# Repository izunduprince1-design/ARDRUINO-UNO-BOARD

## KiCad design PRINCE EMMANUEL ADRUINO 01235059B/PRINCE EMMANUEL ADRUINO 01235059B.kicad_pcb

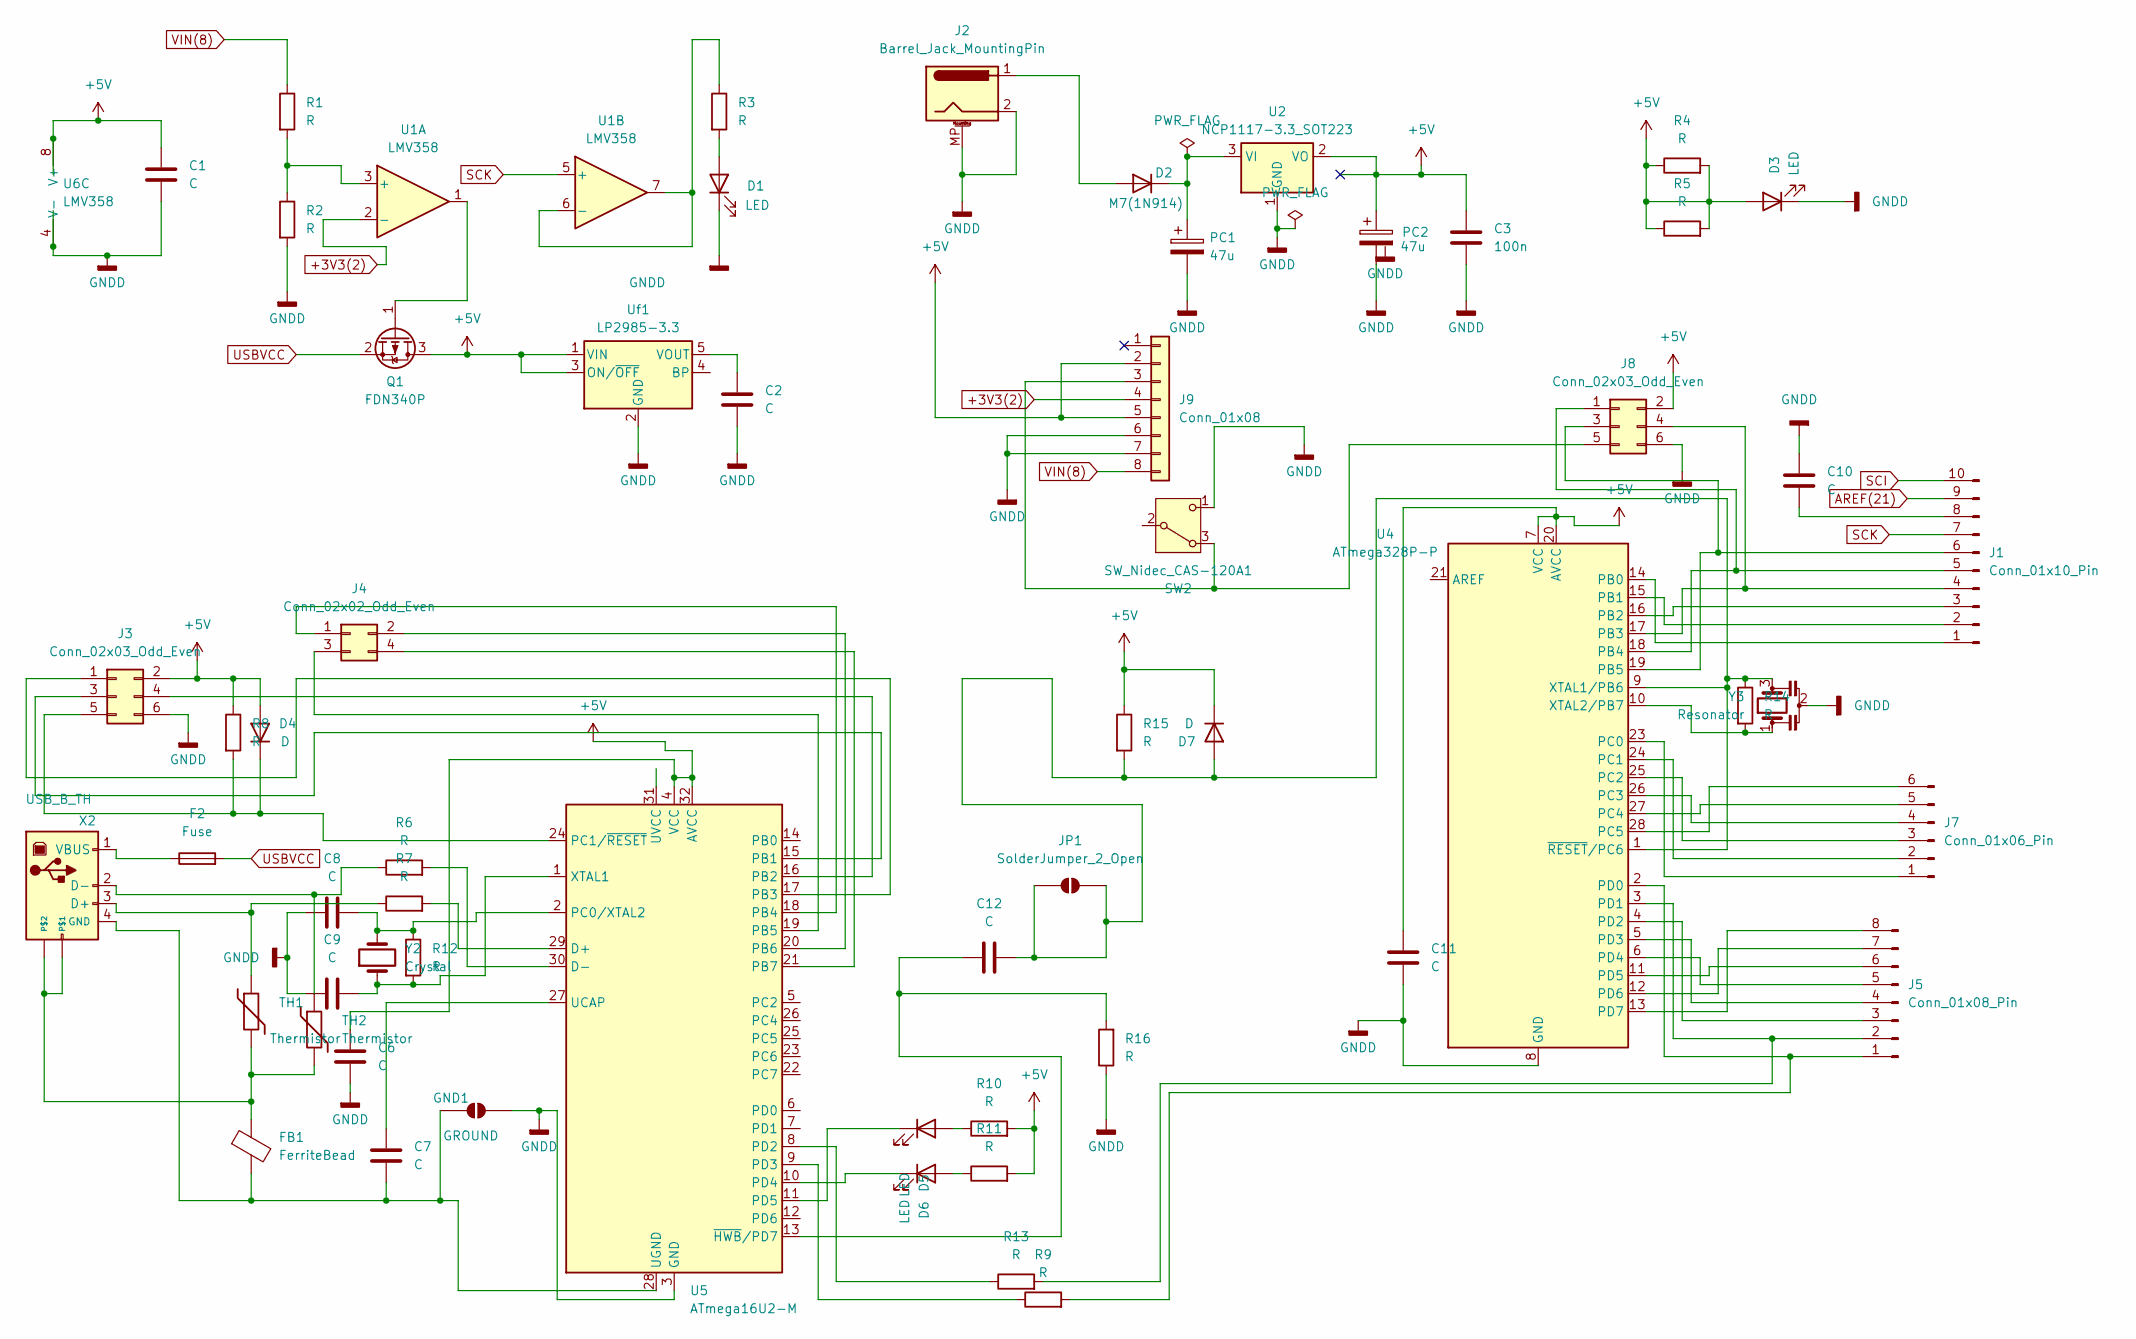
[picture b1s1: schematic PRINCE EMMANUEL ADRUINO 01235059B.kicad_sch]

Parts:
C1, C6, C7, C8, C9, C10, C11, C12: C; C_0603_1608Metric_Pad1.08x0.95mm_HandSolder
C2: C; C_01005_0402Metric
C3: 100n; C_0805_2012Metric_Pad1.18x1.45mm_HandSolder
D1, D3, D5, D6: LED; LED_0805_2012Metric_Pad1.15x1.40mm_HandSolder
D2: M7(1N914); D_SC-80
D4: D; D_01005_0402Metric
D7: D; D_SOD-123
F2: Fuse; Fuse_2920_7451Metric
FB1: FerriteBead; L_0805_2012Metric_Pad1.05x1.20mm_HandSolder
GND1: GROUND; SolderJumper-2_P1.3mm_Open_RoundedPad1.0x1.5mm
J1: Conn_01x10_Pin; PinSocket_1x10_P2.54mm_Vertical
J2: Barrel_Jack_MountingPin; BarrelJack_Horizontal
J3: Conn_02x03_Odd_Even; PinHeader_2x03_P2.54mm_Vertical_SMD
J4: Conn_02x02_Odd_Even; PinSocket_2x02_P2.54mm_Vertical
J5: Conn_01x08_Pin; PinHeader_1x08_P2.54mm_Vertical
J7: Conn_01x06_Pin; PinSocket_1x06_P2.54mm_Vertical
J8: Conn_02x03_Odd_Even; PinHeader_2x03_P2.54mm_Vertical
J9: Conn_01x08; PinSocket_1x08_P2.54mm_Vertical
JP1: SolderJumper_2_Open; SolderJumper-2_P1.3mm_Open_RoundedPad1.0x1.5mm
PC1, PC2: 47u; CP_Elec_6.3x5.4
Q1: FDN340P; SOT-23
R1, R2, R3, R4, R5, R6, R7, R9, R10, R11, R12, R13, R14, R15, R16: R; R_0201_0603Metric_Pad0.64x0.40mm_HandSolder
R8: R; R_0805_2012Metric_Pad1.20x1.40mm_HandSolder
SW2: SW_Nidec_CAS-120A1; SW_Push_1P1T_NO_CK_PTS125Sx43SMTR
TH1, TH2: Thermistor; R_0201_0603Metric_Pad0.64x0.40mm_HandSolder
U1, U6: LMV358; MSOP-8_3x3mm_P0.65mm
U2: NCP1117-3.3_SOT223; SOT-223-3_TabPin2
U4: ATmega328P-P; DIP-28_W7.62mm
U5: ATmega16U2-M; QFN-32-1EP_5x5mm_P0.5mm_EP3.1x3.1mm
Uf1: LP2985-3.3; SOT-23-5
X2: USB_B_TH; USB_B_TE_5787834_Vertical
Y2: Crystal; Crystal_HC49-4H_Vertical
Y3: Resonator; Resonator_SMD_Murata_CSTxExxV-3Pin_3.0x1.1mm_HandSoldering

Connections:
+3V3(2): J9.4, U1.2 (-)
+5V: C1.1, C3.1, C6.1, C11.1, D3.2 (A), D4.2 (A), D7.1 (K), J3.2, J8.2, J9.2, J9.5, PC2.1, Q1.3 (D), R4.1, R4.2, R5.1, R5.2, R8.1, R10.2, R11.2, R15.1, U2.2 (VO), U4.7 (VCC), U4.20 (AVCC), U5.4 (VCC), U5.32 (AVCC), U6.8 (V+), Uf1.1 (VIN), Uf1.3 (ON/~OFF)
AREF(21): J1.9
GNDD: C1.2, C2.2, C3.2, C6.2, C8.1, C9.1, C10.1, C11.2, D1.1 (K), D3.1 (K), GND1.2 (B), J2.2, J2.MP (MountPin), J3.6, J8.6, J9.6, J9.7, PC1.2, PC2.2, R2.2, R16.1, SW2.1 (C_1), U2.1 (GND), U4.8 (GND), U4.22 (GND), U5.3 (GND), U5.33 (GND), U6.4 (V-), Uf1.2 (GND), Y3.2
unnamed: D1.2 (A), R3.2
unnamed: D2.2 (A), J2.1
unnamed: D2.1 (K), PC1.1, U2.3 (VI)
unnamed: D4.1 (K), J3.5, R8.2, U5.24 (PC1/~RESET)
unnamed: D5.2 (A), R10.1
unnamed: D5.1 (K), U5.11 (PD5)
unnamed: D6.2 (A), R11.1
unnamed: D6.1 (K), U5.10 (PD4)
unnamed: C12.2, D7.2 (A), JP1.1 (A), JP1.2 (B), R14.1, R15.2, U4.1 (~RESET/PC6), U4.9 (XTAL1/PB6), Y3.3
unnamed: C7.2, FB1.2, GND1.1 (A), U5.28 (UGND), X2.4 (GND)
unnamed: J1.1, U4.14 (PB0)
unnamed: J1.2, U4.15 (PB1)
unnamed: J1.3, U4.16 (PB2)
unnamed: J1.4, J8.4, U4.17 (PB3)
unnamed: J1.5, J8.1, U4.18 (PB4)
unnamed: J1.6, J8.3, U4.19 (PB5)
unnamed: C10.2, J1.8
unnamed: J3.1, U5.17 (PB3)
unnamed: J3.3, U5.15 (PB1)
unnamed: J3.4, U5.16 (PB2)
unnamed: J4.1, U5.18 (PB4)
unnamed: J4.2, U5.20 (PB6)
unnamed: J4.3, U5.19 (PB5)
unnamed: J4.4, U5.21 (PB7)
unnamed: J5.1, R9.2, U4.2 (PD0)
unnamed: J5.2, R13.2, U4.3 (PD1)
unnamed: J5.3, U4.4 (PD2)
unnamed: J5.4, U4.5 (PD3)
unnamed: J5.5, U4.6 (PD4)
unnamed: J5.6, U4.11 (PD5)
unnamed: J5.7, U4.12 (PD6)
unnamed: J5.8, U4.13 (PD7)
unnamed: J7.1, U4.23 (PC0)
unnamed: J7.2, U4.24 (PC1)
unnamed: J7.3, U4.25 (PC2)
unnamed: J7.4, U4.26 (PC3)
unnamed: J7.5, U4.27 (PC4)
unnamed: J7.6, U4.28 (PC5)
unnamed: J8.5, J9.3, SW2.3 (A)
unnamed: Q1.1 (G), U1.1
unnamed: R1.2, R2.1, U1.3 (+)
unnamed: R3.1, U1.6 (-), U1.7
unnamed: R14.2, U4.10 (XTAL2/PB7), Y3.1
unnamed: R7.2, U5.29 (D+)
unnamed: R6.2, U5.30 (D-)
unnamed: C8.2, R12.1, U5.2 (PC0/XTAL2), Y2.2
unnamed: R13.1, U5.8 (PD2)
unnamed: R9.1, U5.9 (PD3)
unnamed: C7.1, U5.27 (UCAP)
unnamed: C9.2, R12.2, U5.1 (XTAL1), Y2.1
unnamed: C12.1, R16.2, U5.13 (~HWB/PD7)
unnamed: C2.1, Uf1.5 (VOUT)
unnamed: R7.1, TH1.1, X2.3 (D+)
unnamed: R6.1, TH2.1, X2.2 (D-)
unnamed: FB1.1, TH1.2, TH2.2, X2.
unnamed: F2.1, X2.1 (VBUS)
SCI: J1.10
SCK: J1.7, U1.5 (+)
USBVCC: F2.2, Q1.2 (S)
VIN(8): J9.8, R1.1

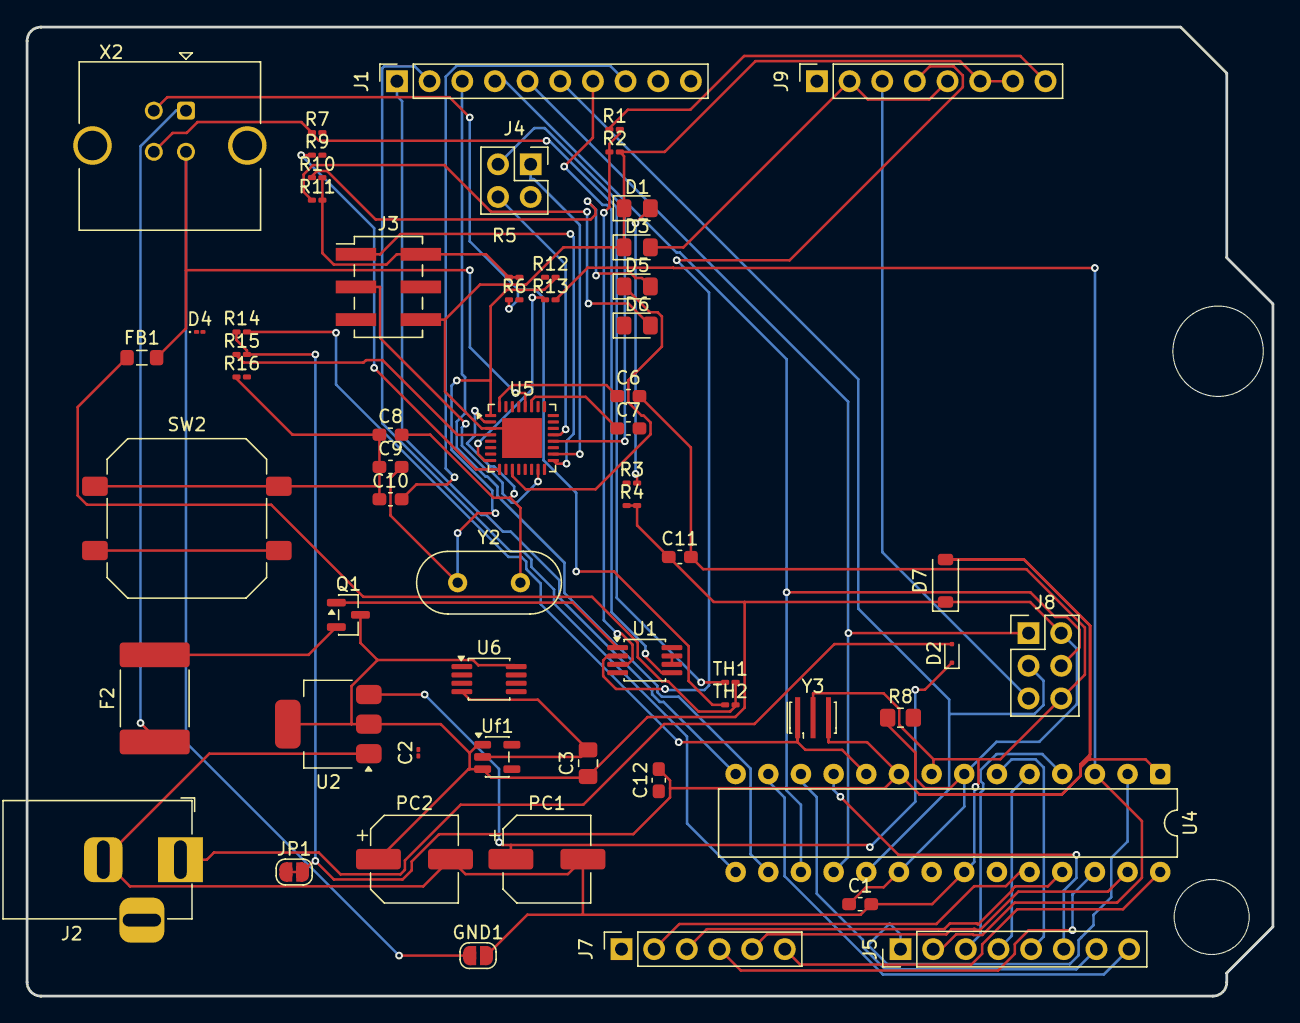
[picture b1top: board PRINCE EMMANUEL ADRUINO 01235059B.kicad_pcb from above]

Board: 2 copper layers, 96.9 x 75.4 mm, 60 parts (0 on the bottom side), 62 nets.
